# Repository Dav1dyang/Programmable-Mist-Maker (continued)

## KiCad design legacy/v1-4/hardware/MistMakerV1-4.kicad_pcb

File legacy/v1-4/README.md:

# V1.4 — Historical Reference

This folder is the original (and only) released revision of the Programmable Mist Maker, kept intact for anyone reproducing the kit as documented in the root `README.md`.

It has been **superseded** by the modular variant tree under [`../../variants/`](../../variants/). New work targets one of the four V0.x variants (Xiao Extension Kit, Battery Kit, Block Kit, I2C MultiPack Kit). V1.4 will not receive new firmware features.

📖 **[Full guide, including the quirks and their fixes](https://docs.byproductlab.com/boards/legacy-v1-4/)**

Contents:

- `hardware/` — KiCad project, schematic + PCB PDFs, BOM.
- `example-code/` — Two reference sketches: `WithLibrary/` (using the `MistMaker` Arduino library) and `WithoutLibrary-108kHz_Output_3V3_XIAOC6/` (bare-metal 108.7 kHz PWM).
- `EnclosureDesignMaterials/` — STEP/STL/DXF files for the 3D-printed shell.

Safety, cleaning, and known-issues guidance still lives in the root `README.md`.

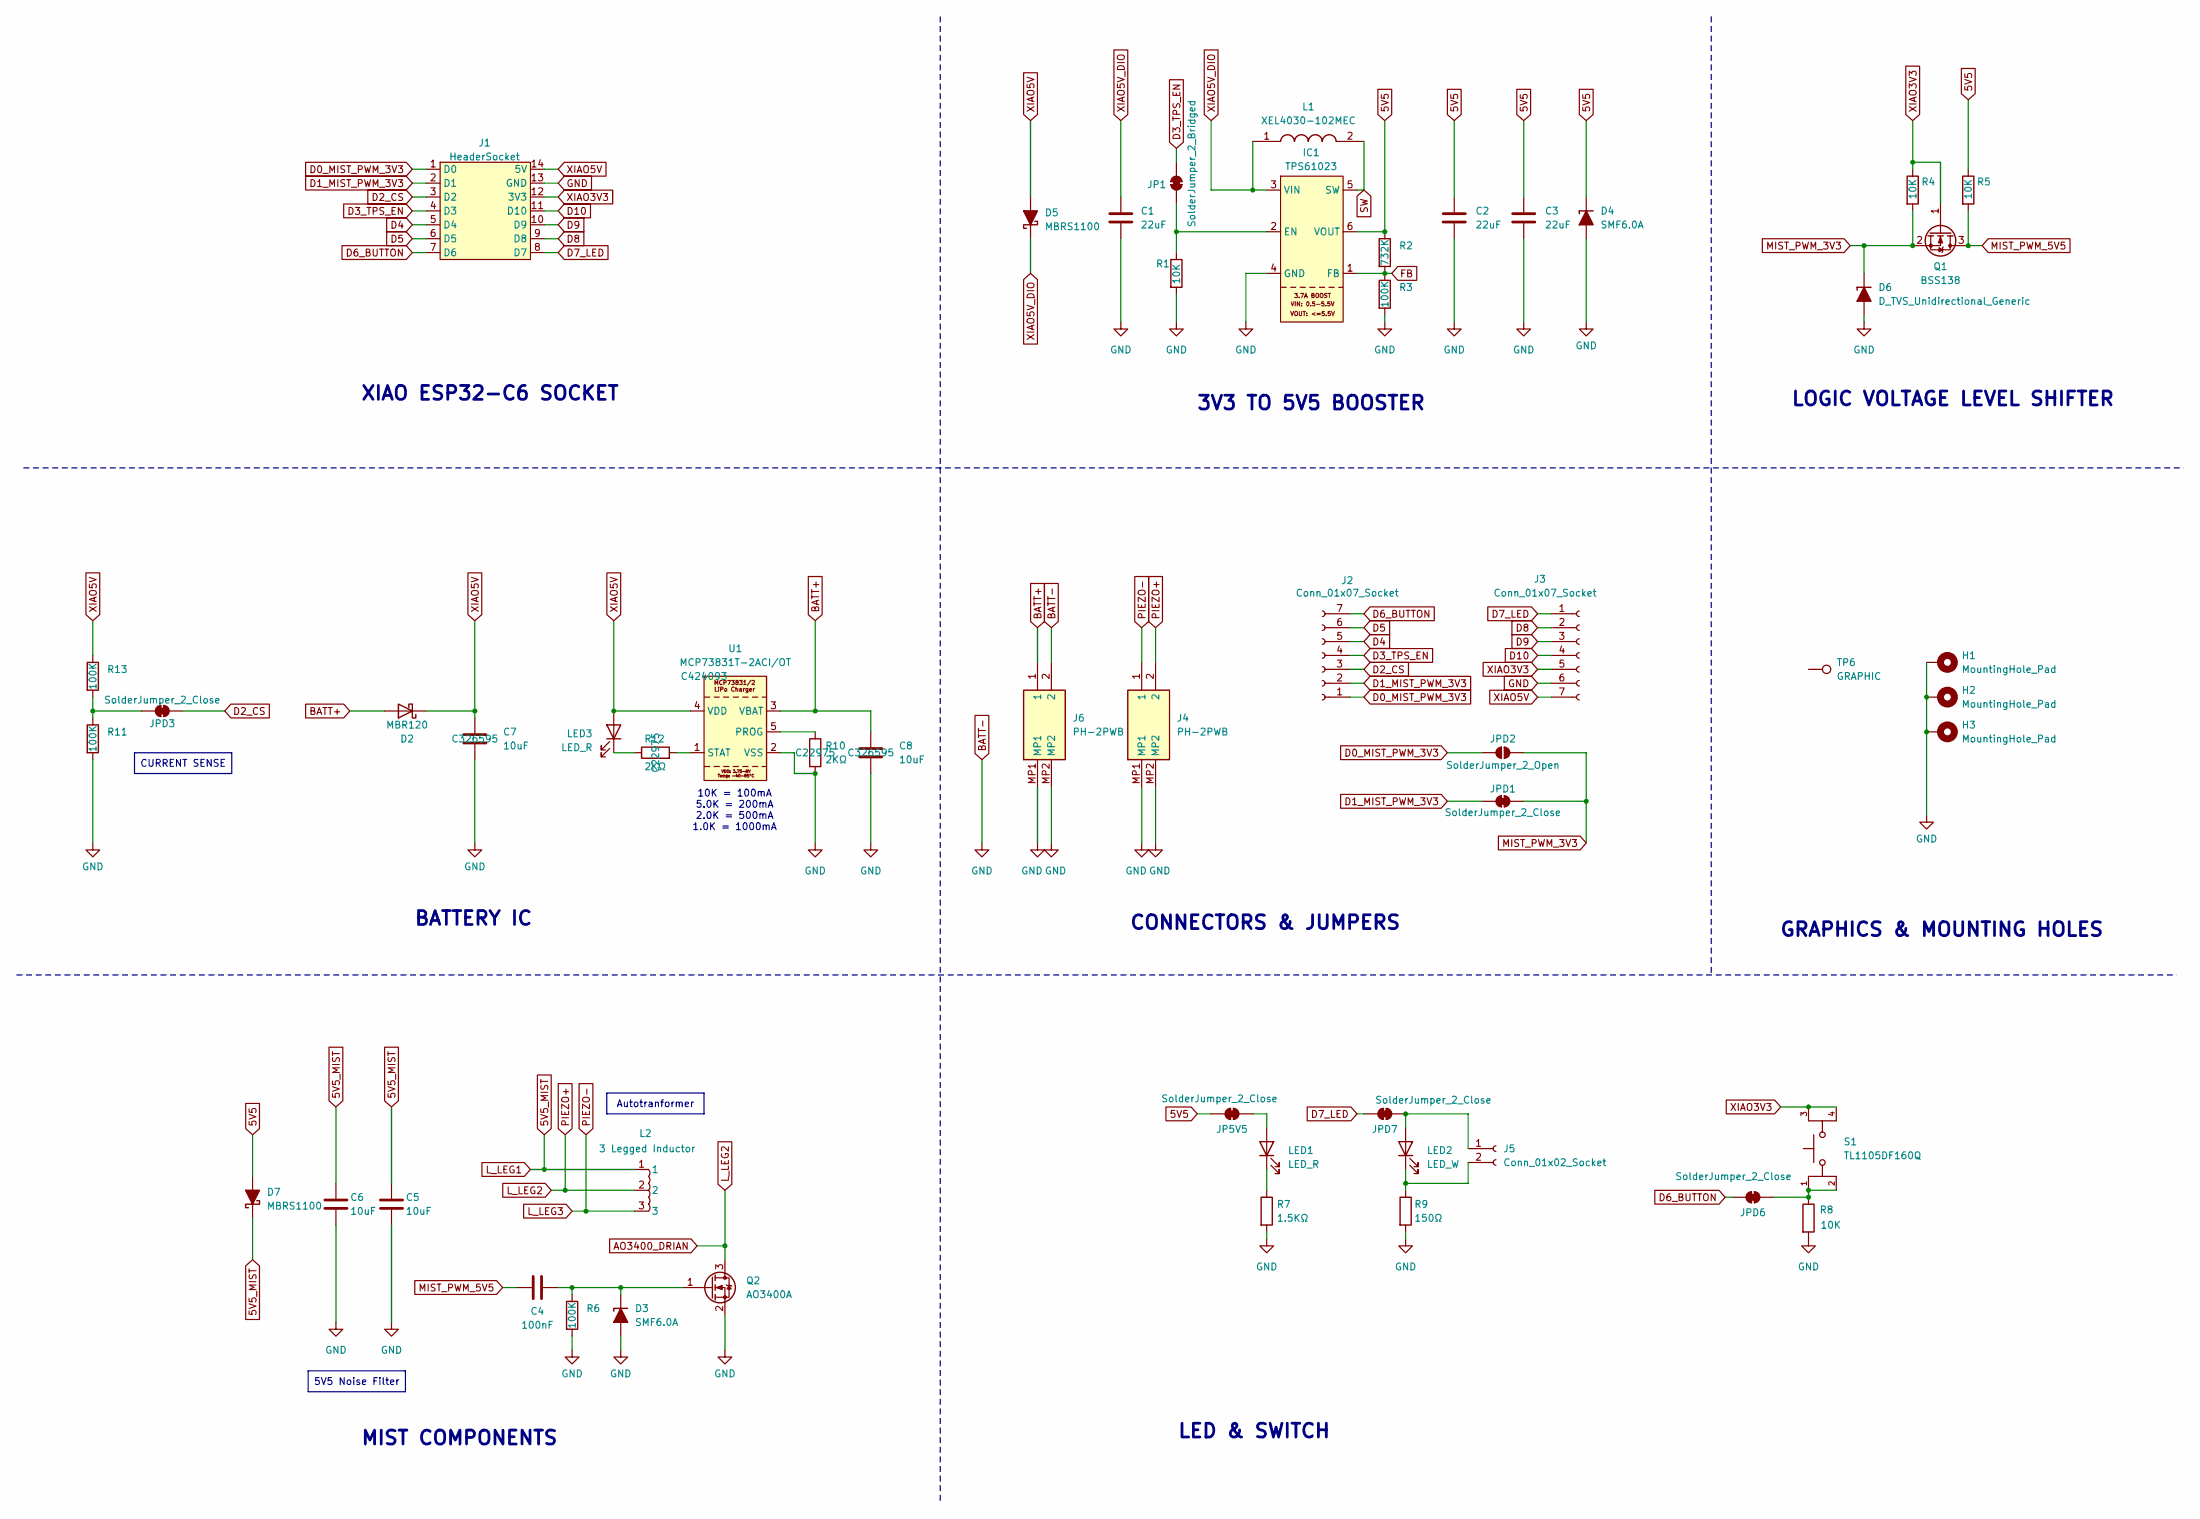
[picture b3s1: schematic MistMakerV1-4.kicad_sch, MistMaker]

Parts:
C1, C2, C3: 22uF; C_0805_2012Metric_Pad1.18x1.45mm_HandSolder; JLC C98190
C4: 100nF; C_0603_1608Metric; JLC C3011705
C5, C6: 10uF; C_0805_2012Metric_Pad1.18x1.45mm_HandSolder; JLC C326595
C7, C8: 10uF; C_0805_2012Metric; JLC C326595
D2: MBR120; D_SOD-123F; JLC C81143
D3, D4: SMF6.0A; D_SOD-123F; JLC C19077499
D5, D7: MBRS1100; D_SMB_Min_Silk; JLC C82068
D6: D_TVS_Unidirectional_Generic; D_SOD-323_HandSoldering; JLC C20617916
H1, H2, H3: MountingHole_Pad; MountingHole_2.2mm_M2_DIN965_Pad
IC1: TPS61023; SOTFL50P160X60-6N; JLC C919459
J1: HeaderSocket; XIAO-ESP32C6-DIP
J2, J3: Conn_01x07_Socket; PinSocket_1x07_P2.54mm_Vertical
J4, J6: PH-2PWB; PH2PWB; Manufacturer_Part_Number PH-2PWB; JLC C2905019
J5: Conn_01x02_Socket; PinHeader_1x02_P2.54mm_less_Marks
JP1: SolderJumper_2_Bridged; SolderJumper-2_P1.3mm_Bridged_RoundedPad1.0x1.5mm
JP5V5: SolderJumper_2_Close; SolderJumper-2_P1.3mm_Bridged_RoundedPad1.0x1.5mm
JPD1, JPD3, JPD6, JPD7: SolderJumper_2_Close; SolderJumper-2_P1.3mm_Bridged_RoundedPad1.0x1.5mm
JPD2: SolderJumper_2_Open; SolderJumper-2_P1.3mm_Open_RoundedPad1.0x1.5mm
L1: XEL4030-102MEC; XEL4030102MEC; Manufacturer_Part_Number XEL4030-102MEC; Mouser Part Number 994-XEL4030-102MEC
L2: 3 Legged Inductor; 3_Leg_Autotransformer
LED1, LED3: LED_R; LED_0603_1608Metric; JLC C2286
LED2: LED_W; LED_0603_1608Metric; JLC C2290
Q1: BSS138; SOT-23; JLC C40912
Q2: AO3400A; SOT-23; JLC C20917
R1: 10K; R_0603_1608Metric_Pad0.98x0.95mm_HandSolder; JLC C98220
R2: 732K; R_0603_1608Metric_Pad0.98x0.95mm_HandSolder; JLC C246003
R3: 100K; R_0603_1608Metric_Pad0.98x0.95mm_HandSolder; JLC C14675
R4, R5: 10K; R_0805_2012Metric_Pad1.20x1.40mm_HandSolder; JLC C17414
R6, R11, R13: 100K; R_0603_1608Metric; JLC C14675
R7: 1.5KΩ; R_0603_1608Metric; JLC C114668
R8: 10K; R_0805_2012Metric; JLC C17414
R9: 150Ω; R_0603_1608Metric; JLC C114608
R10, R12: 2KΩ; R_0603_1608Metric; JLC C22975
S1: TL1105DF160Q; SW_TL1105DF160Q; PARTREV A; JLC C273469
TP6: GRAPHIC; DUCKY_ICON
U1: MCP73831T-2ACI/OT; BATT_Charger_SOT-23-5_Min_Silk; JLC C424093

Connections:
5V5: C2.1, C3.1, D4.1 (K), D7.2 (A), IC1.6 (VOUT), JP5V5.1 (A), R2.1, R5.1
5V5_MIST: C5.1, C6.1, D7.1 (K), L2.1
AO3400_DRIAN: J4.2, L2.2, Q2.3 (D)
BATT+: C8.1, D2.2 (A), J6.1, U1.3 (VBAT)
BATT-: C1.2, C2.2, C3.2, C5.2, C6.2, C7.2, C8.2, D3.2 (A), D4.2 (A), D6.2 (A), H1.1, H2.1, H3.1, IC1.4 (GND), J1.13 (GND), J3.6, J4.MP1, J4.MP2, J6.2, J6.MP1, J6.MP2, Q2.2 (S), R1.2, R3.2, R6.2, R7.2, R8.2, R9.2, R10.2, R11.2, U1.2 (VSS)
D0_MIST_PWM_3V3: J1.1 (D0), J2.1, JPD2.1 (A)
D1_MIST_PWM_3V3: J1.2 (D1), J2.2, JPD1.1 (A)
D2_CS: J1.3 (D2), J2.3, JPD3.1 (A)
D3_TPS_EN: J1.4 (D3), J2.4, JP1.1 (A)
D4: J1.5 (D4), J2.5
D5: J1.6 (D5), J2.6
D6_BUTTON: J1.7 (D6), J2.7, JPD6.1 (A)
D7_LED: J1.8 (D7), J3.1, JPD7.1 (A)
D8: J1.9 (D8), J3.2
D9: J1.10 (D9), J3.3
D10: J1.11 (D10), J3.4
FB: IC1.1 (FB), R2.2, R3.1
L_LEG3: J4.1, L2.3
MIST_PWM_3V3: D6.1 (K), JPD1.2 (B), JPD2.2 (B), Q1.2 (S), R4.2
MIST_PWM_5V5: C4.2, Q1.3 (D), R5.2
unnamed: C4.1, D3.1 (K), Q2.1 (G), R6.1
unnamed: IC1.2 (EN), JP1.2 (B), R1.1
unnamed: J5.1, JPD7.2 (B), LED2.2 (A)
unnamed: J5.2, LED2.1 (K), R9.1
unnamed: JP5V5.2 (B), LED1.2 (A)
unnamed: JPD3.2 (B), R11.1, R13.2
unnamed: JPD6.2 (B), R8.1, S1.1, S1.2
unnamed: LED1.1 (K), R7.1
unnamed: LED3.1 (K), R12.1
unnamed: R10.1, U1.5 (PROG)
unnamed: R12.2, U1.1 (STAT)
SW: IC1.5 (SW), L1.2
XIAO3V3: J1.12 (3V3), J3.5, Q1.1 (G), R4.1, S1.3, S1.4
XIAO5V: C7.1, D2.1 (K), D5.2 (A), J1.14 (5V), J3.7, LED3.2 (A), R13.1, U1.4 (VDD)
XIAO5V_DIO: C1.1, D5.1 (K), IC1.3 (VIN), L1.1

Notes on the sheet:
GRAPHICS & MOUNTING HOLES
CONNECTORS & JUMPERS
BATTERY IC
XIAO ESP32-C6 SOCKET
LED & SWITCH
10K = 100mA 5.0K = 200mA 2.0K = 500mA 1.0K = 1000mA
LOGIC VOLTAGE LEVEL SHIFTER
3V3 TO 5V5 BOOSTER
MIST COMPONENTS
Autotranformer
5V5 Noise Filter
CURRENT SENSE

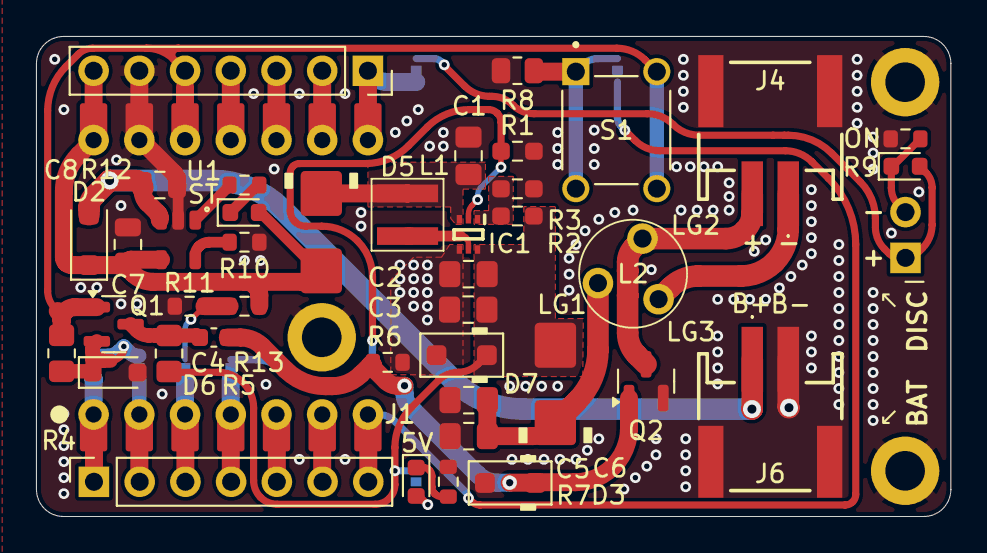
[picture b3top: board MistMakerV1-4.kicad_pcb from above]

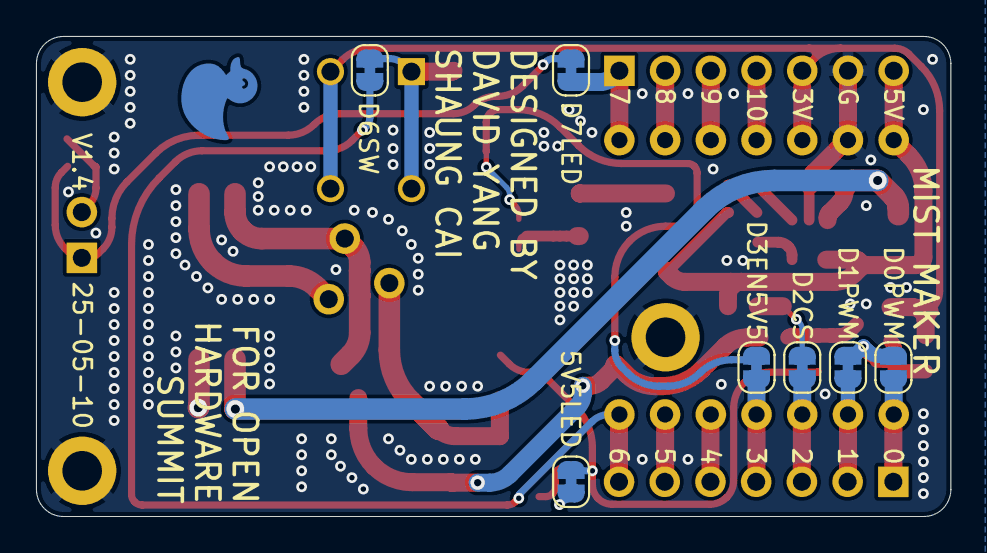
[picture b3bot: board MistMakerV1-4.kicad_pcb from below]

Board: 2 copper layers, 50.8 x 26.7 mm, 54 parts (8 on the bottom side), 35 nets.

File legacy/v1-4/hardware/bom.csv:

Designator,Footprint,Quantity,Value,LCSC Part #
"C1, C2, C3",0805,3,22uF,C98190
C4,0603,1,100nF,C3011705
"C5, C6, C7, C8",0805,4,10uF,C326595
D2,D_SOD-123F,1,MBR120,C81143
"D3, D4",D_SOD-123F,2,SMF6.0A,C19077499
"D5, D7",D_SMB_Min_Silk,2,MBRS1100,C82068
D6,D_SOD-323_HandSoldering,1,D_TVS_Unidirectional_Generic,C20617916
IC1,SOTFL50P160X60-6N,1,TPS61023,C919459
"J4, J6",PH2PWB,2,PH-2PWB,C2905019
L1,XEL4030102MEC,1,XEL4030-102MEC,C5441341
"LED1, LED3",0603,2,LED_R,C2286
LED2,0603,1,LED_W,C2290
Q1,SOT-23,1,BSS138,C40912
Q2,SOT-23,1,AO3400A,C20917
R1,0603,1,10K,C98220
"R10, R12",0603,2,2KΩ,C22975
"R11, R13, R3, R6",0603,4,100K,C14675
R2,0603,1,732K,C246003
"R4, R5, R8",0805,3,10K,C17414
R7,0603,1,1.5KΩ,C114668
R9,0603,1,150Ω,C114608
S1,SW_TL1105DF160Q,1,TL1105DF160Q,C273469
U1,BATT_Charger_SOT-23-5_Min_Silk,1,MCP73831T-2ACI/OT,C424093

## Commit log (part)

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2025-05-13 includes all pcb files and update readme
2025-05-13 Includes BOM
2025-05-22 Update Read Me
2025-05-22 update images
2025-05-27 added git.ignore and updated example folders
2025-05-27 added 3dPrint Models
2025-05-27 updated 3d models into readme
2025-05-27 README changes
2025-05-27 added README
2025-05-28 Update README.md
    Update the product name to align with the manufacturer's, and add a hyperlink for deeper dive
2025-05-28 changed folder name
2025-05-28 formatting README
2025-05-28 Edited README
2025-07-01 added Hackster.io link
2025-07-02 added Cleaning instructions
2025-07-02 formatting
2026-05-13 Restructure into variants/ tree and add Block Kit Phase A firmware
    Move the V1.4 hardware, example code, and enclosure files under legacy/v1-4/
    and scaffold a new variants/ tree (xiao-extension-kit, battery-kit, block-kit,
    i2c-multipack-kit) so each kit can evolve independently without touching the
    others or the historical reference.
    Ship the Block Kit V0.1 bring-up firmware (Phase A) under variants/block-kit/
    firmware/BlockKit_Test/. Multi-.ino layout with pins.h as the single source
2026-05-13 Fix three review findings on Phase A firmware
    - led_driver.ino: replace g_is31.clear() (not in stock Adafruit lib) with a
    manual zero loop over the 14 populated positions. Should compile against
    both stock and David's fork.
    - BlockKit_Test.ino: drop String from the serial command parser, switch to a
    fixed 32-char buffer + simple integer-tail parser. Matches the plan's
    no-dynamic-allocation / no-String rule.
2026-05-13 Clean up root: merge typo'd git.igonre into .gitignore, drop tracked .DS_Stores
    - Delete git.igonre (typo of .gitignore that Git never recognized) and move
    its actually-useful ignore patterns (Arduino build artifacts, IDE caches,
    macOS junk) into the real .gitignore.
    - Untrack two .DS_Store files that slipped into the V1.4 example folders.
    They were already ignored going forward via the new patterns; this removes
    the historical copies.
2026-05-13 Stage missing .gitignore update from cleanup commit
    Previous commit deleted git.igonre and untracked the .DS_Stores but the
    merged ignore patterns were unstaged so they didn't actually land. This
    commit adds them.
2026-05-13 Fix g_lastTickMs name collision across .ino files
    Arduino IDE concatenates every .ino in a sketch folder into a single
    translation unit before compiling. That means file-scope `static` doesn't
    actually limit visibility per-file -- three sibling files all declared
    `static uint32_t g_lastTickMs` and the compiler saw three redefinitions of
    the same name.
    Prefix each with its module: g_btnLastTickMs (button), g_ledLastTickMs
2026-05-13 Add pins.h portability shim so sketch builds on QT Py too
    XIAO ESP32-C6 and XIAO ESP32-S3 expose XIAO-style D0..D7 pin labels in their
    variants/pins_arduino.h, but Adafruit QT Py boards do not (they use A0..A3 +
    named SPI/I2C pins). The sketch is XIAO-shape hardware in practice, but the
    user wants it to also `compile` on a QT Py for porting / sanity checks.
    Add an `#if !defined(D0)` fallback at the top of pins.h that picks valid
    GPIOs for ESP32-S3 family boards without Dx labels. These are NOT the real
2026-05-13 Move reed switch from D1 to D10
    D1 was originally repurposed (via blue-wire rework) from its schematic role
    as the alt-PWM destination through JP02. Switching the reed to D10 -- which
    is unused on the Block Kit V0.1 schematic -- has three small advantages:
    - D1 stays in its documented schematic role; JP02 behavior is no longer
    entangled with the reed wiring.
    - D10 is physically opposite D0 (mist PWM) on the XIAO socket footprint,
2026-05-13 Fix LED driver: address Matrix B via setLEDPWM + LED_MAP
    The previous driver used drawPixel(x,y,…) from Adafruit_GFX, which writes
    the IS31FL3731's Matrix A. Block Kit V0.1 populates Matrix B only (CB1/CB2),
    so drawPixel calls "succeed" silently but never light a real LED. That was
    the cause of the dark column user reported during bring-up.
    Rewrite to David's working approach (his bench-validated test sketch):
    - Use setLEDPWM(lednum, pwm, 0) which writes the chip's PWM register space
2026-05-13 Harden input pins + add [STAT] live diagnostic
    David's bench tests reveal that in this firmware D10 reads LOW continuously
    (reed always "present") and D6 reads HIGH continuously (false long-press)
    even though his minimal test sketch reads D10 correctly with INPUT_PULLUP.
    That points at something in our richer setup() sequence disturbing the pin
    state after pinMode -- moving the input inits to the end and adding a
    defensive pull-down should clear both.
2026-05-13 Defensively re-apply pinMode in every reed and button poll
    David confirmed both D10 (reed) and D6 (button) read correctly in his
    minimal test sketches, but in this firmware D10 sits stuck LOW and D6 stuck
    HIGH. The pin numbers, wiring, and pinMode arguments are all correct. The
    only difference between his minimal sketch and this firmware is the rest of
    setup() -- Wire.begin, LEDC attaches, IS31FL3731 begin, ADC config, ledInit.
    Something in that chain on XIAO ESP32-C6 + arduino-esp32 v3.3.8 leaves the
2026-05-13 Fix pin-map bug: use ARDUINO_XXX guard for QT Py fallback, add `m` mute cmd
    Root cause of nearly every bring-up symptom this evening (D10 stuck LOW,
    D6 stuck HIGH, mean_mA=0, mist not running, current sense reading nothing):
    pins.h had a portability fallback guarded by `#if !defined(D0)`. The XIAO
    ESP32-C6 platform declares D0..D10 as C++ constants (`static const uint8_t
    D0 = 0;`), not as preprocessor macros. The C preprocessor cannot see C++
    constants, so `#if !defined(D0)` is ALWAYS true. The QT Py fallback was
2026-05-13 Rewrite pins.h with explicit per-board PIN_* blocks (drop Dx macro shim)
    The previous pins.h tried to make the sketch portable by #define-ing Dx
    macros for boards that don't expose XIAO-style pin labels. That approach
    backfired twice:
    1) David's question "shouldn't it be just D1, D2 etc?" is correct on
    XIAO boards. The XIAO platform header already exposes D0..D10 as
    C++ constants; remapping them via #define adds nothing.
2026-05-13 Phase A UX overhaul: unified level + 3-state machine + luxurious ramps
    Major rework of the user experience based on bench testing feedback:
    UX changes
    ----------
    * One `g_userLevel` (0..255) drives BOTH mist PWM duty and LED ring
    brightness. Long-press the button to ramp it; LEDs and mist follow
    together. Mist duty = (level * 127) / 255 so level 255 = 50% PWM =
2026-05-13 Add concise ARCHITECTURE.md for Block Kit Phase A firmware
    One-page technical overview sitting alongside README.md. Covers:
    - stack (MCU, toolchain, conventions)
    - hardware (3-PCB role split)
    - pin map (XIAO ESP32-C6, with GPIO numbers)
    - state machine diagram + transition table
    - unified-level model (userLevel / targetLevel / currentLevel)
2026-05-13 Apply Phase A code review fixes (5 medium + 3 nit)
    Findings from a deep code review (Plan agent, opus) — applied the medium-
    severity bugs and the three NITs that earn their weight; skipped the
    verbose-style NITs (table-driven banner, clamp helper, etc.) since the
    inline versions read fine and the user picked "Medium" cleanup scope.
    MEDIUM:
    * led_driver.ino: phaseQ8 multiply overflowed uint32_t every ~262 s
2026-05-13 LED redesign: BREATH idle + SWIRL chase docked + cinematic removal
    User feedback: the ring is a 14-LED vertical strip (top=LED 1, bottom=
    LED 14), not a ring; the previous "always uniform breath" effect didn't
    match the intent. New behavior, agreed via question round before coding:
    * IDLE_LEDS_ON (boot default): all 14 LEDs do a soft uniform breath at
    the user level. Short-press still toggles to IDLE_LEDS_OFF (mute) and
    back. Boot now lands here instead of IDLE_LEDS_OFF.
2026-05-13 LED redesign v2: unified continuous-modulation envelope (no modes)
    User feedback on the previous chase-style implementation: too bright in
    idle, breath not visible, chase felt snappy not premium, the dock
    transition "had nothing" visible. Round of clarifying questions chose:
    * Idle = "very dim & dramatic breath" (10..45 % range, 6.5 s cycle)
    * Docked = "single broad swell" drifting bottom→top, ~4.5 s per traversal,
    all LEDs always lit (not a chase head + dark tail)
2026-05-13 Fix Arduino IDE build: drop template<>, specialize smoothToward16
    The Arduino IDE's auto-prototype generator inserts a forward declaration
    BEFORE the `template<typename T>` line, producing 'T was not declared in
    this scope' errors. arduino-cli doesn't reproduce this so the previous
    commit slipped through CI-equivalent local verification.
    Both call sites pass uint16_t, so a concrete signature is the right fix
    (no need for the templated helper). Renamed to smoothToward16 to keep
2026-05-13 Bump LED_BREATH_PEAK 38 → 80 for smoother idle gradient
    At peak=38 the gamma LUT maps the entire breath sweep onto PWM 0 and 1
    only — so what the user saw was effectively a slow blink, not a breath.
    Raw peak 80 maps to PWM 10/255 (≈4 %), and the sweep now passes through
    11 distinct PWM levels (0..10), giving the eye a smooth perceptual
    gradient. Still firmly in dim-ambient territory — peak brightness is
    4 % so the ring stays a soft glow, not a nightlight.
2026-05-14 Sync mist drive to LED wave; short-press hides LEDs only
    While in RUNNING, mist drive is now modulated by the wave swell's
    gaussian intensity sampled at the piezo's position (1 LED above the top
    of the strip via MIST_PIEZO_OFFSET_LEDS_Q8). The mist rises with the
    visible swell, peaks once the wave has crossed the top (where the piezo
    physically sits), then dims down together with the top LED as the wave
    exits off-screen above. Trough is set to 92/256 ≈ 36% of full so the
2026-05-14 Fix flash on docked→idle restore: snap WAVE→BREATH while strip is dark
    When the wave has just dimmed to baseLevel=0 and we enter IDLE, the
    previous code called ledSetMode(BREATH) which kicked off a 1.1 s
    WAVE→BREATH crossfade. During the parallel fast level-restore the
    crossfade engine kept rendering WAVE (raw 92..255) blended with BREATH
    (raw 0..LED_BREATH_PEAK) while baseLevel rose 0→255 — WAVE's much
    higher raw dominated mid-restore and produced a visible flash (peak
2026-05-14 Add BlockKit_BringUp sketch for raw per-feature bench verification
    Minimal single-file Arduino sketch that exercises each Block Kit V0.1
    peripheral in isolation — no state machine, no animations, no smoother.
    Button press toggles boost rail + mist (50% PWM) + all 14 LEDs at a
    fixed brightness. Serial commands:
    t toggle (same as button)
    w LED chase, top-to-bottom, 1 s per LED
2026-05-14 Promote Block Kit firmware to production: WiFi/OTA/web UI + runtime config
    Rename BlockKit_Test/ to BlockKit_Production/ and add the production
    pieces that turn the bench firmware into a daily-use device.
    Runtime config (config.h + config.ino)
    Every UX tunable that used to be a constexpr in pins.h is now a
    field on a global `Config cfg` struct backed by NVS (Preferences,
    namespace `blockkit`). pins.h keeps each value as CFG_DEFAULT_*;
2026-05-14 Fix Block Kit Production firmware compile errors
    Five issues caught when the previous PR was compiled in Arduino IDE:
    1. CfgBlob struct moved from config.ino to config.h
    The Arduino IDE auto-generates forward declarations for .ino-file
    functions and inserts them at the TOP of the preprocessed file,
    BEFORE the file's own struct definitions. packBlob(CfgBlob&) and
    unpackBlob(const CfgBlob&) had their prototypes inserted before
